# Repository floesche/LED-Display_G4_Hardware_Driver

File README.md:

---
title: Panel PCB 2017
parent: Hardware
grand_parent: Generation 4
---

# G4 Panel

```
├── Design      - OrCAD `.BRD` file
├── Production  - Gerber + BOM
└── Schematic   - pdf with schematic
```

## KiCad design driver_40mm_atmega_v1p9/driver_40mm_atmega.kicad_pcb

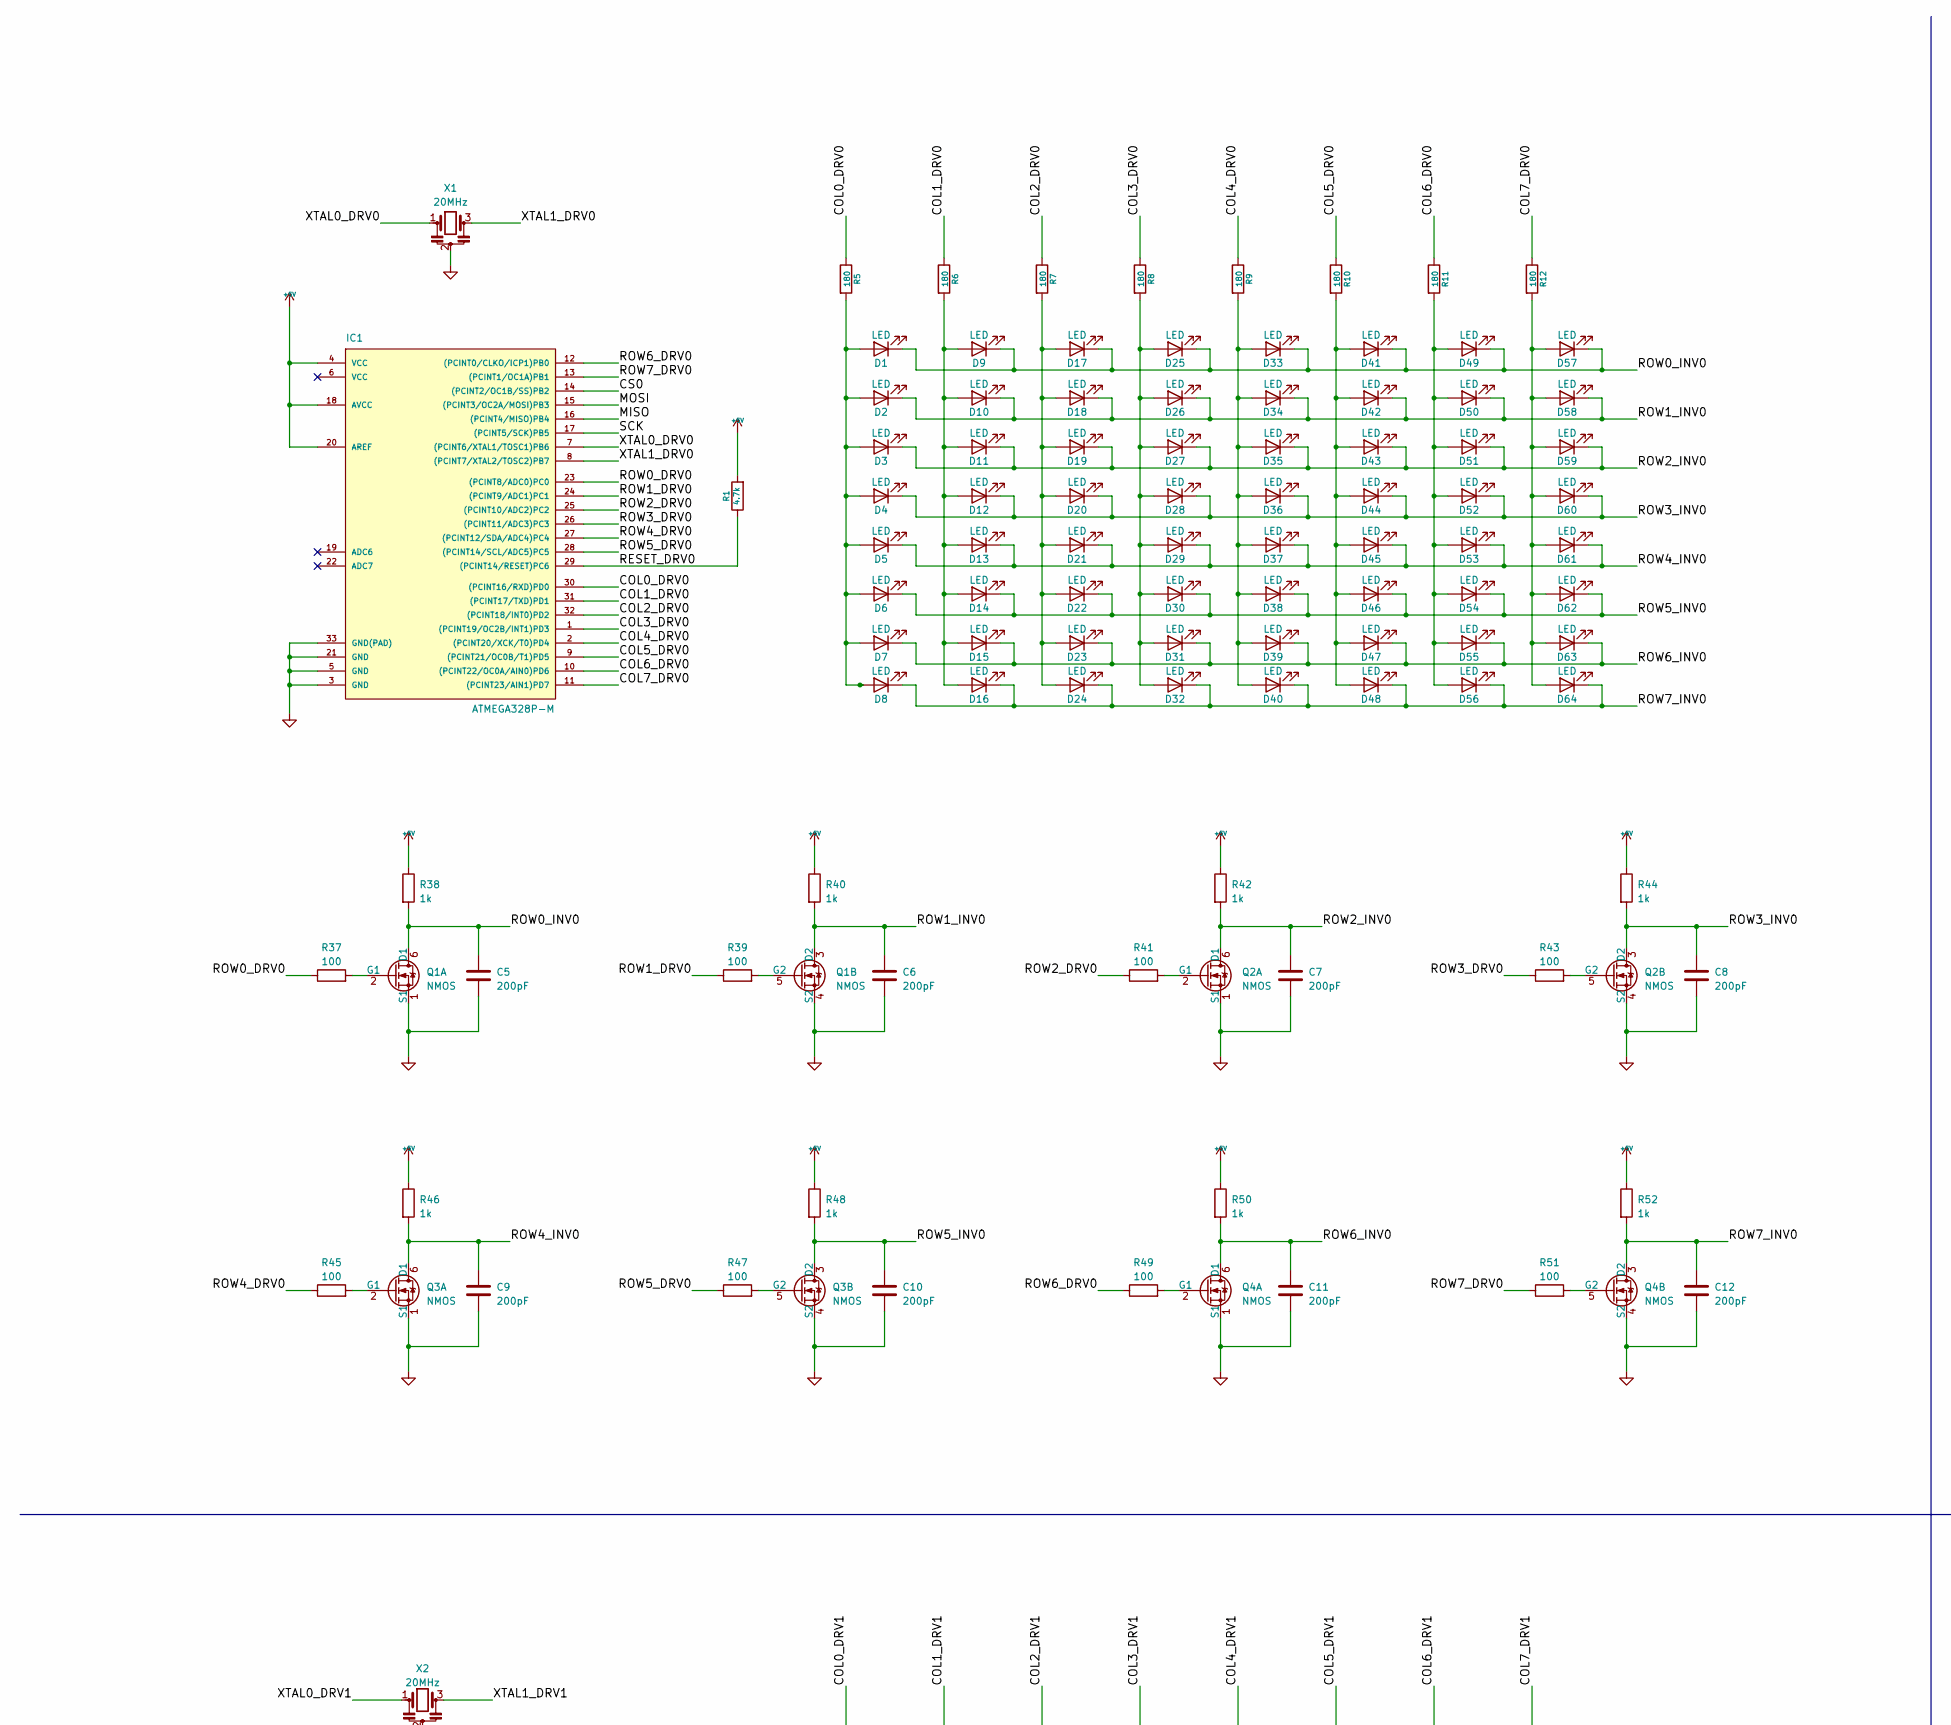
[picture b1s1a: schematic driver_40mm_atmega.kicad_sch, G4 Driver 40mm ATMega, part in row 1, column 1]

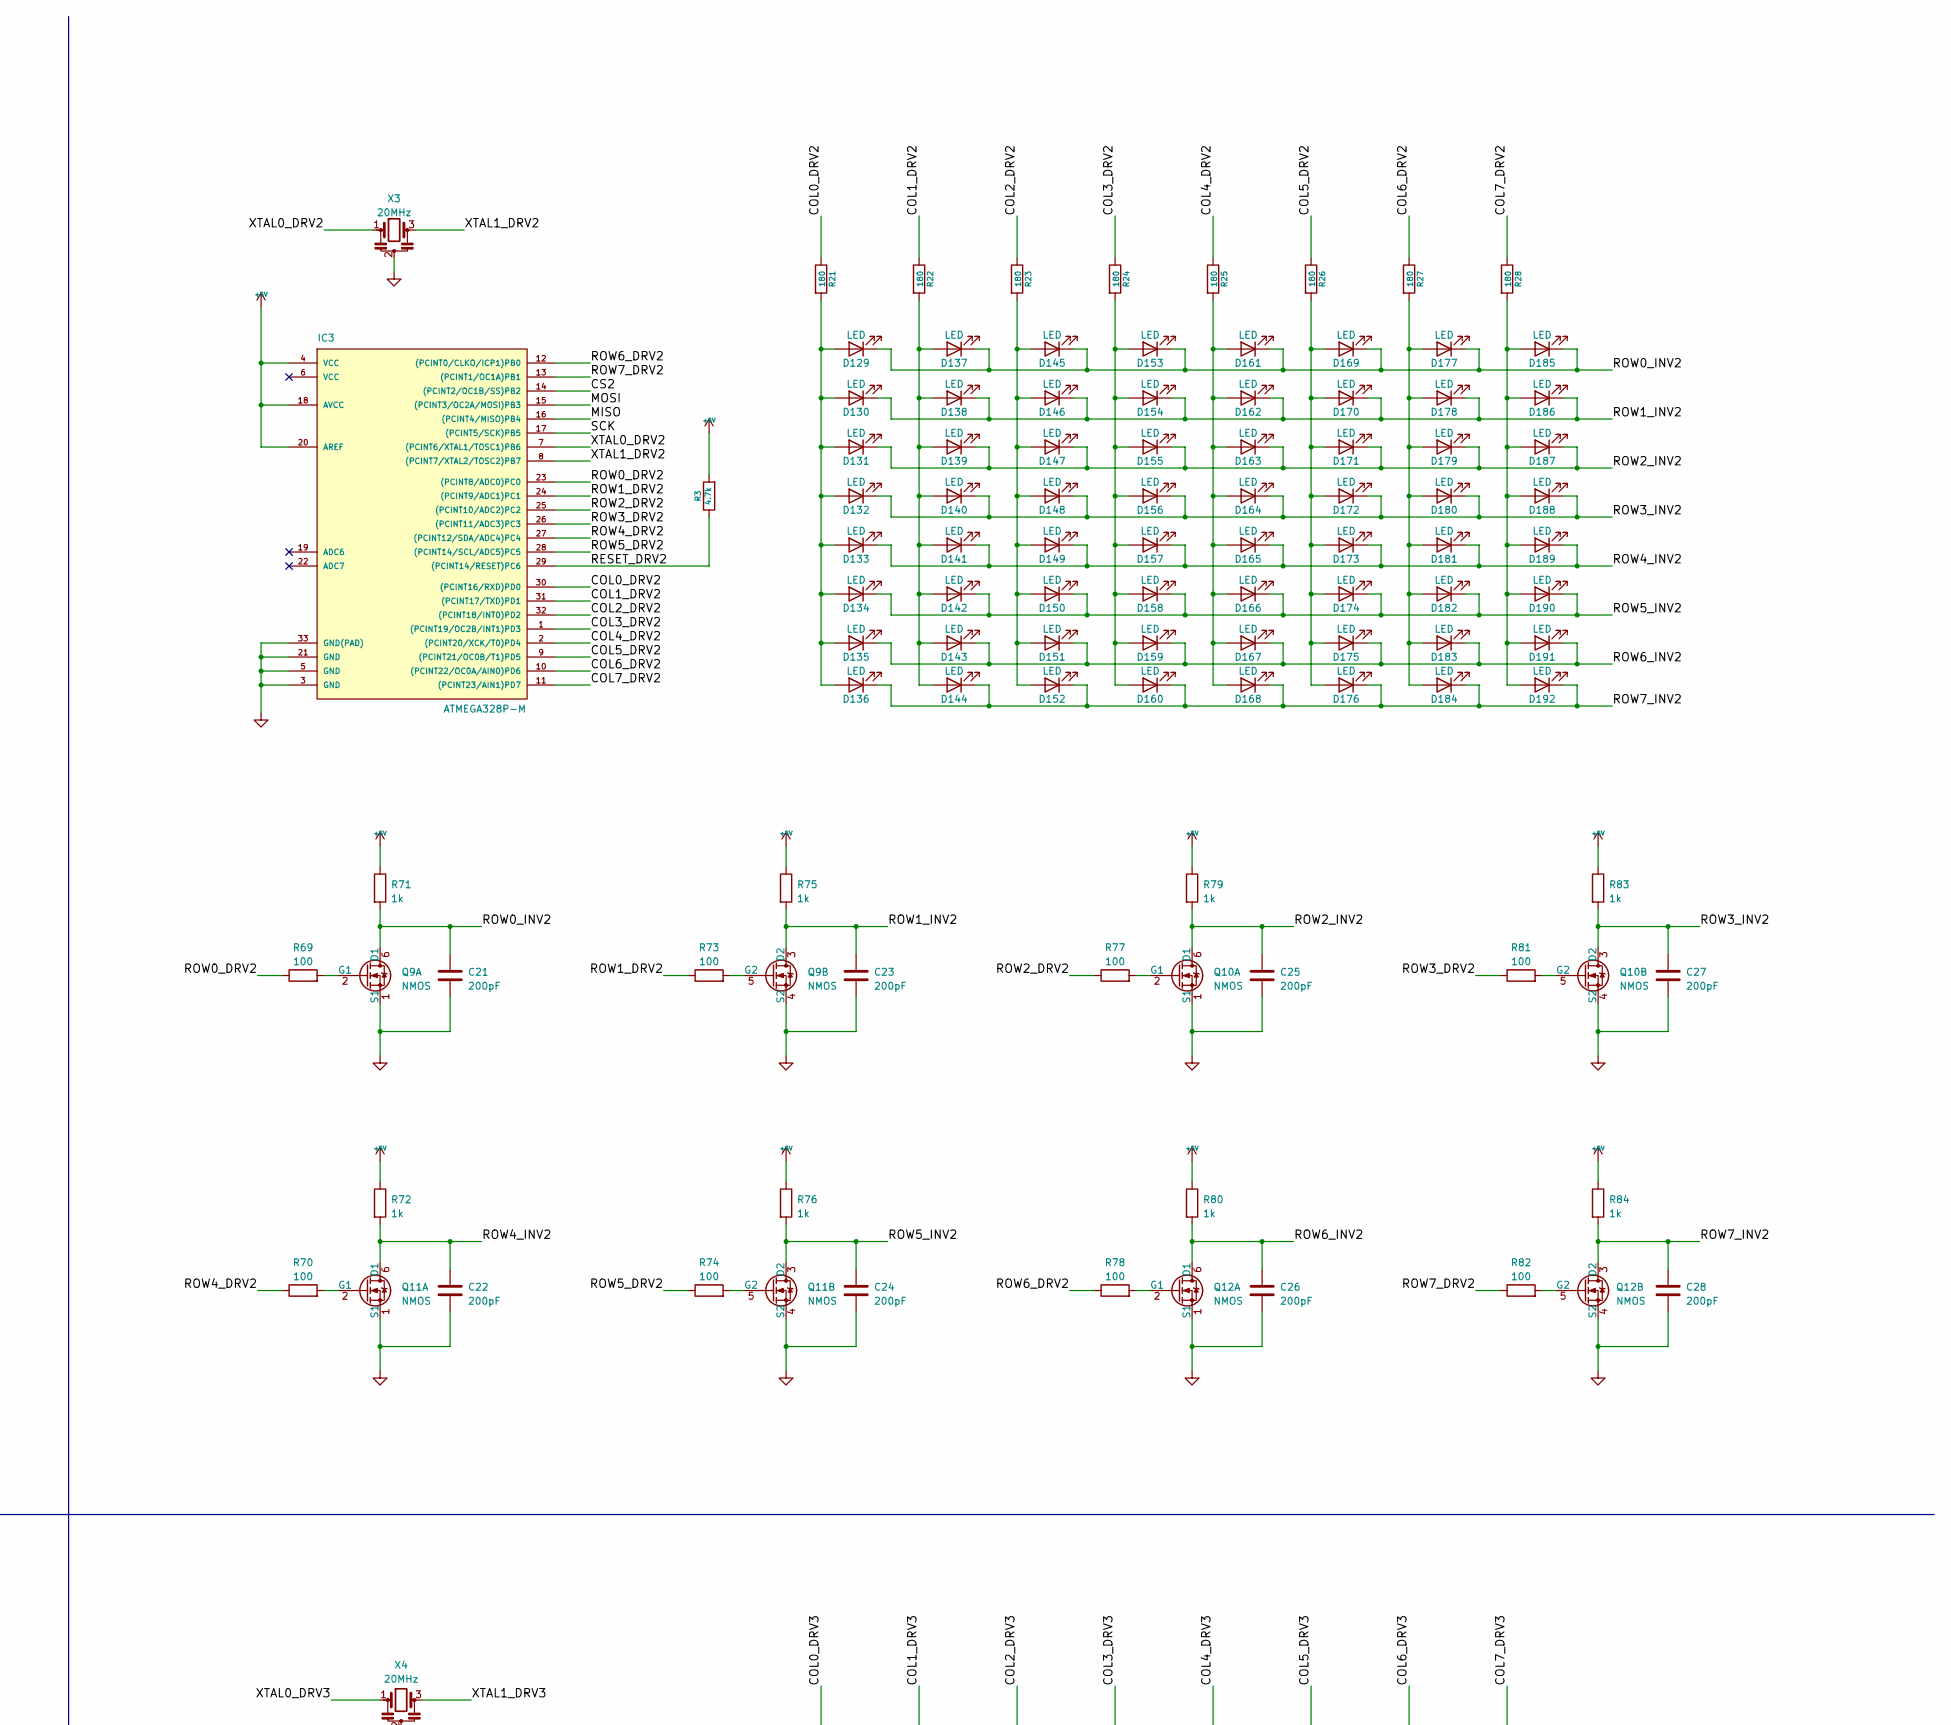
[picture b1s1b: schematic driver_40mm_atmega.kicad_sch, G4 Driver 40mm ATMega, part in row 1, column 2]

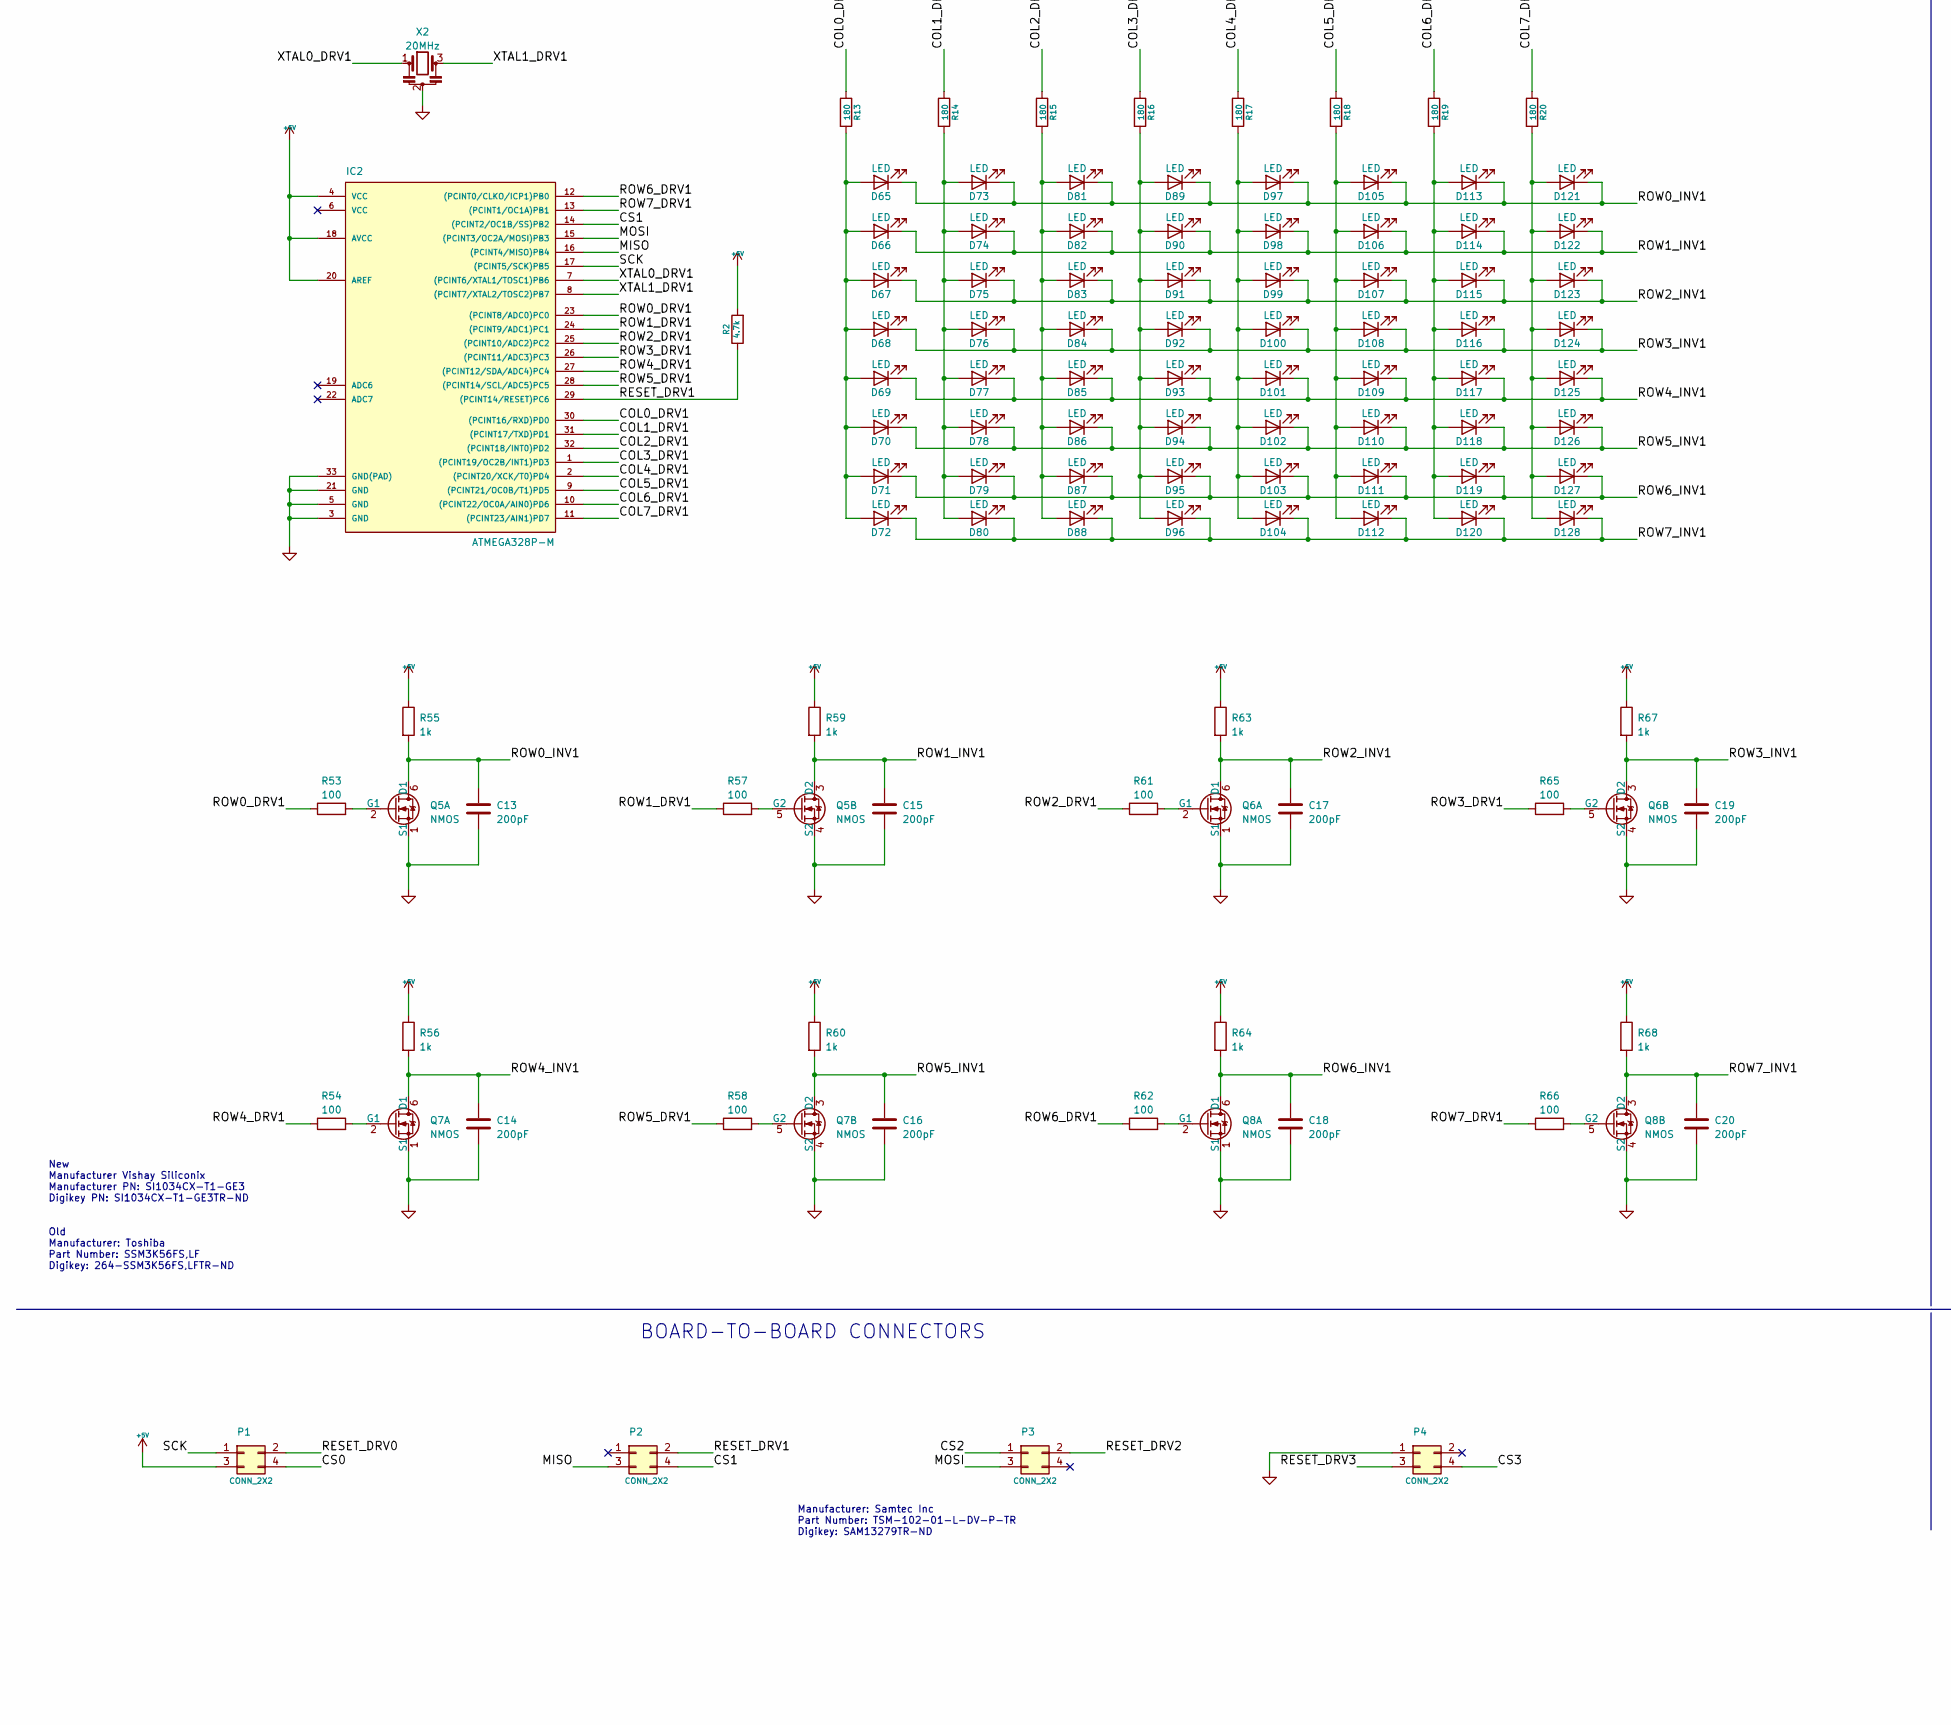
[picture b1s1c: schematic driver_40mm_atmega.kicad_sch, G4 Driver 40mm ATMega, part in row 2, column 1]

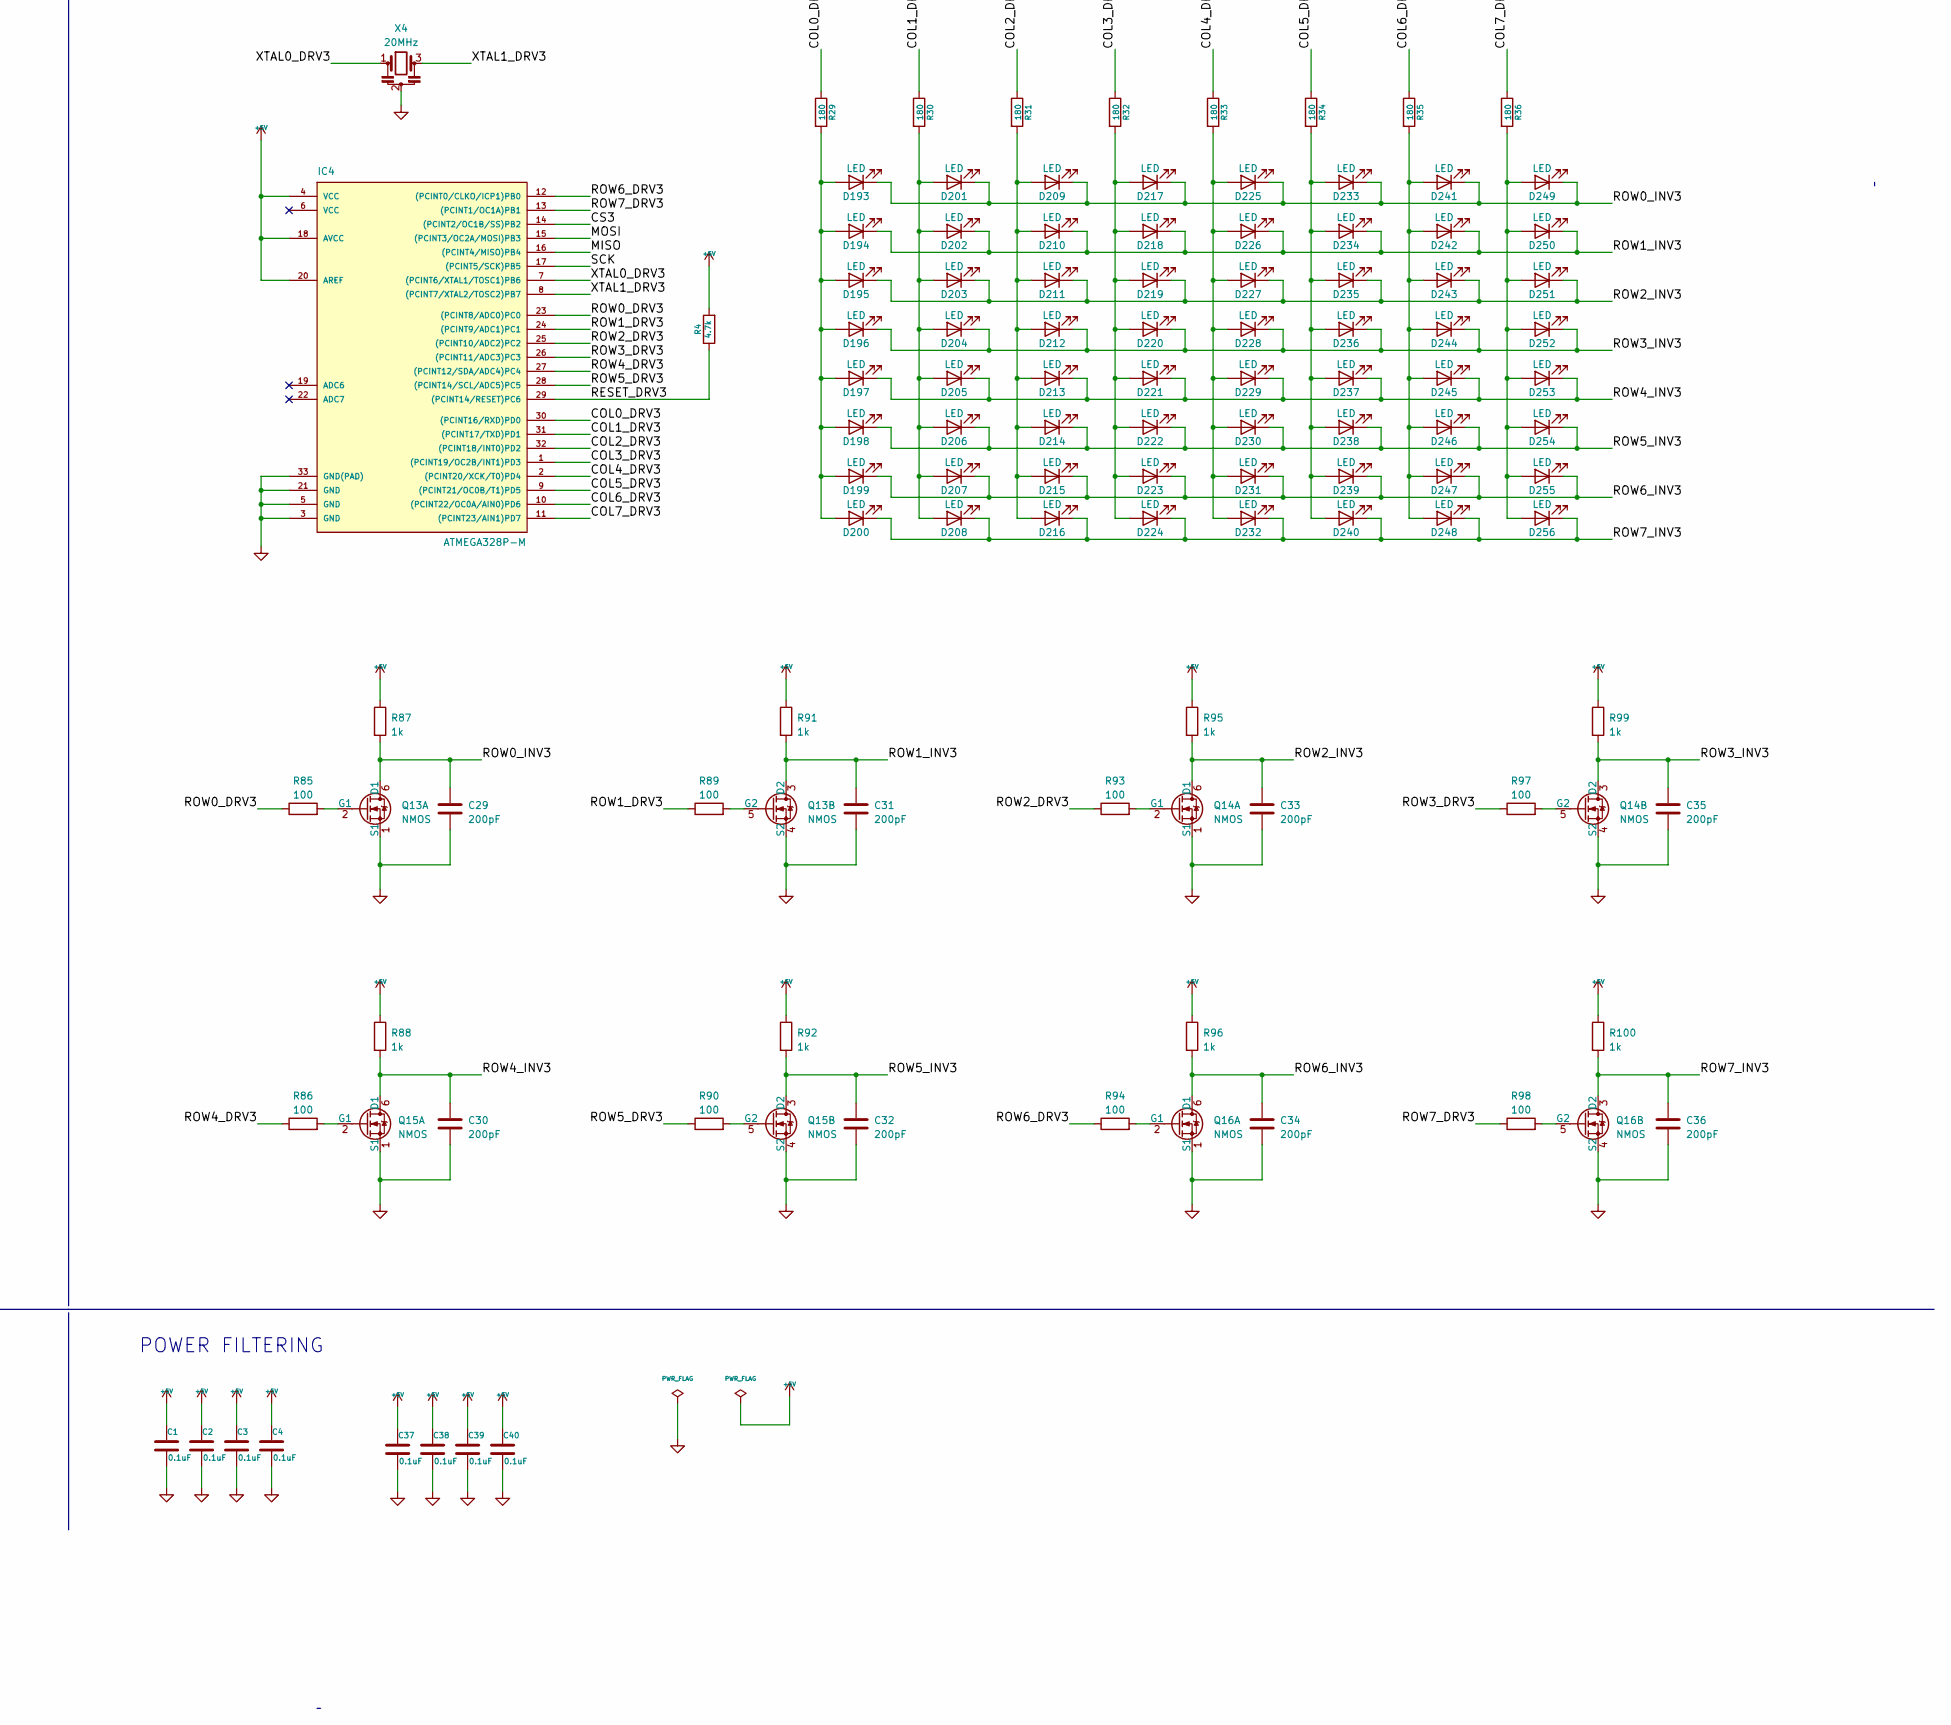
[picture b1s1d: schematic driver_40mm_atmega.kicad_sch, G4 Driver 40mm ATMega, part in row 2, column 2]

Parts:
C1, C2, C3, C4, C37, C38, C39, C40: 0.1uF; C_0201_0603Metric; JLCPCB PN C76937
C5, C6, C7, C8, C9, C10, C11, C12, C13, C14, C15, C16, C17, C18, C19, C20, C21, C22, C23, C24, C25, C26, C27, C28, C29, C30, C31, C32, C33, C34, C35, C36: 200pF; C_0201_0603Metric; JLCPCB PN C565508
D1, D2, D3, D4, D5, D6, D7, D8, D9, D10, D11, D12, D13, D14, D15, D16, D17, D18, D19, D20, D21, D22, D23, D24, D25, D26, D27, D28, D29, D30, D31, D32, D33, D34, D35, D36, D37, D38, D39, D40, D41, D42, D43, D44, D45, D46, D47, D48, D49, D50, D51, D52, D53, D54, D55, D56, D57, D58, D59, D60, D61, D62, D63, D64, D65, D66, D67, D68, D69, D70, D71, D72, D73, D74, D75, D76, D77, D78, D79, D80, D81, D82, D83, D84, D85, D86, D87, D88, D89, D90, D91, D92, D93, D94, D95, D96, D97, D98, D99, D100, D101, D102, D103, D104, D105, D106, D107, D108, D109, D110, D111, D112, D113, D114, D115, D116, D117, D118, D119, D120, D121, D122, D123, D124, D125, D126, D127, D128, D129, D130, D131, D132, D133, D134, D135, D136, D137, D138, D139, D140, D141, D142, D143, D144, D145, D146, D147, D148, D149, D150, D151, D152, D153, D154, D155, D156, D157, D158, D159, D160, D161, D162, D163, D164, D165, D166, D167, D168, D169, D170, D171, D172, D173, D174, D175, D176, D177, D178, D179, D180, D181, D182, D183, D184, D185, D186, D187, D188, D189, D190, D191, D192, D193, D194, D195, D196, D197, D198, D199, D200, D201, D202, D203, D204, D205, D206, D207, D208, D209, D210, D211, D212, D213, D214, D215, D216, D217, D218, D219, D220, D221, D222, D223, D224, D225, D226, D227, D228, D229, D230, D231, D232, D233, D234, D235, D236, D237, D238, D239, D240, D241, D242, D243, D244, D245, D246, D247, D248, D249, D250, D251, D252, D253, D254, D255, D256: LED; LED_0402_1005Metric; JLCPCB PN C5160718
IC1, IC2, IC3, IC4: ATMEGA328P-M; QFN-32-1EP_5x5mm_P0.5mm_EP3.1x3.1mm; JLCPCB PN C2651951
P1, P2, P3, P4: CONN_2X2; PinHeader_2x02_P2.54mm_Vertical_SMD; JLCPCB PN C7499901
Q1, Q2, Q3, Q4, Q5, Q6, Q7, Q8, Q9, Q10, Q11, Q12, Q13, Q14, Q15, Q16: NMOS; SC-89-6; JLCPCB PN C145239
R1, R2, R3, R4: 4.7k; R_0201_0603Metric; JLCPCB PN C226669
R5, R6, R7, R8, R9, R10, R11, R12, R13, R14, R15, R16, R17, R18, R19, R20, R21, R22, R23, R24, R25, R26, R27, R28, R29, R30, R31, R32, R33, R34, R35, R36: 180; R_0201_0603Metric; JLCPCB PN C5141103
R37, R39, R41, R43, R45, R47, R49, R51, R53, R54, R57, R58, R61, R62, R65, R66, R69, R70, R73, R74, R77, R78, R81, R82, R85, R86, R89, R90, R93, R94, R97, R98: 100; R_0201_0603Metric; JLCPCB PN C2991668
R38, R40, R42, R44, R46, R48, R50, R52, R55, R56, R59, R60, R63, R64, R67, R68, R71, R72, R75, R76, R79, R80, R83, R84, R87, R88, R91, R92, R95, R96, R99, R100: 1k; R_0201_0603Metric; JLCPCB PN C102689
X1, X2, X3, X4: 20MHz; Resonator_SMD_Murata_CSTxExxV-3Pin_3.0x1.1mm; JLCPCB PN C882604

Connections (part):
+5V: C1.1, C2.1, C3.1, C4.1, C37.1, C38.1, C39.1, C40.1, IC1.4 (VCC), IC1.18 (AVCC), IC1.20 (AREF), IC2.4 (VCC), IC2.18 (AVCC), IC2.20 (AREF), IC3.4 (VCC), IC3.18 (AVCC), IC3.20 (AREF), IC4.4 (VCC), IC4.18 (AVCC), IC4.20 (AREF), P1.3, R1.2, R2.2, R3.2, R4.2, R38.1, R40.1, R42.1, R44.1, R46.1, R48.1, R50.1, R52.1, R55.1, R56.1, R59.1, R60.1, R63.1, R64.1, R67.1, R68.1, R71.1, R72.1, R75.1, R76.1, R79.1, R80.1, R83.1, R84.1, R87.1, R88.1, R91.1, R92.1, R95.1, R96.1, R99.1, R100.1
/COL0_DRV0: IC1.30 ((PCINT16/RXD)PD0), R5.1
/COL0_DRV1: IC2.30 ((PCINT16/RXD)PD0), R13.1
/COL0_DRV2: IC3.30 ((PCINT16/RXD)PD0), R21.1
/COL0_DRV3: IC4.30 ((PCINT16/RXD)PD0), R29.1
/COL1_DRV0: IC1.31 ((PCINT17/TXD)PD1), R6.1
/COL1_DRV1: IC2.31 ((PCINT17/TXD)PD1), R14.1
/COL1_DRV2: IC3.31 ((PCINT17/TXD)PD1), R22.1
/COL1_DRV3: IC4.31 ((PCINT17/TXD)PD1), R30.1
/COL2_DRV0: IC1.32 ((PCINT18/INT0)PD2), R7.1
/COL2_DRV1: IC2.32 ((PCINT18/INT0)PD2), R15.1
/COL2_DRV2: IC3.32 ((PCINT18/INT0)PD2), R23.1
/COL2_DRV3: IC4.32 ((PCINT18/INT0)PD2), R31.1
/COL3_DRV0: IC1.1 ((PCINT19/OC2B/INT1)PD3), R8.1
/COL3_DRV1: IC2.1 ((PCINT19/OC2B/INT1)PD3), R16.1
/COL3_DRV2: IC3.1 ((PCINT19/OC2B/INT1)PD3), R24.1
/COL3_DRV3: IC4.1 ((PCINT19/OC2B/INT1)PD3), R32.1
/COL4_DRV0: IC1.2 ((PCINT20/XCK/T0)PD4), R9.1
/COL4_DRV1: IC2.2 ((PCINT20/XCK/T0)PD4), R17.1
/COL4_DRV2: IC3.2 ((PCINT20/XCK/T0)PD4), R25.1
/COL4_DRV3: IC4.2 ((PCINT20/XCK/T0)PD4), R33.1
/COL5_DRV0: IC1.9 ((PCINT21/OC0B/T1)PD5), R10.1
/COL5_DRV1: IC2.9 ((PCINT21/OC0B/T1)PD5), R18.1
/COL5_DRV2: IC3.9 ((PCINT21/OC0B/T1)PD5), R26.1
/COL5_DRV3: IC4.9 ((PCINT21/OC0B/T1)PD5), R34.1
/COL6_DRV0: IC1.10 ((PCINT22/OC0A/AIN0)PD6), R11.1
/COL6_DRV1: IC2.10 ((PCINT22/OC0A/AIN0)PD6), R19.1
/COL6_DRV2: IC3.10 ((PCINT22/OC0A/AIN0)PD6), R27.1
/COL6_DRV3: IC4.10 ((PCINT22/OC0A/AIN0)PD6), R35.1
/COL7_DRV0: IC1.11 ((PCINT23/AIN1)PD7), R12.1
/COL7_DRV1: IC2.11 ((PCINT23/AIN1)PD7), R20.1
/COL7_DRV2: IC3.11 ((PCINT23/AIN1)PD7), R28.1
/COL7_DRV3: IC4.11 ((PCINT23/AIN1)PD7), R36.1
/CS0: IC1.14 ((PCINT2/OC1B/SS)PB2), P1.4
/CS1: IC2.14 ((PCINT2/OC1B/SS)PB2), P2.4
/CS2: IC3.14 ((PCINT2/OC1B/SS)PB2), P3.1
/CS3: IC4.14 ((PCINT2/OC1B/SS)PB2), P4.4
/MISO: IC1.16 ((PCINT4/MISO)PB4), IC2.16 ((PCINT4/MISO)PB4), IC3.16 ((PCINT4/MISO)PB4), IC4.16 ((PCINT4/MISO)PB4), P2.3
/MOSI: IC1.15 ((PCINT3/OC2A/MOSI)PB3), IC2.15 ((PCINT3/OC2A/MOSI)PB3), IC3.15 ((PCINT3/OC2A/MOSI)PB3), IC4.15 ((PCINT3/OC2A/MOSI)PB3), P3.3
/RESET_DRV0: IC1.29 ((PCINT14/RESET)PC6), P1.2, R1.1
/RESET_DRV1: IC2.29 ((PCINT14/RESET)PC6), P2.2, R2.1
/RESET_DRV2: IC3.29 ((PCINT14/RESET)PC6), P3.2, R3.1
/RESET_DRV3: IC4.29 ((PCINT14/RESET)PC6), P4.3, R4.1
/ROW0_DRV0: IC1.23 ((PCINT8/ADC0)PC0), R37.1
/ROW0_DRV1: IC2.23 ((PCINT8/ADC0)PC0), R53.1
/ROW0_DRV2: IC3.23 ((PCINT8/ADC0)PC0), R69.1
/ROW0_DRV3: IC4.23 ((PCINT8/ADC0)PC0), R85.1
/ROW0_INV0: C5.1, D1.1 (K), D9.1 (K), D17.1 (K), D25.1 (K), D33.1 (K), D41.1 (K), D49.1 (K), D57.1 (K), Q1.6 (D1), R38.2
/ROW0_INV1: C13.1, D65.1 (K), D73.1 (K), D81.1 (K), D89.1 (K), D97.1 (K), D105.1 (K), D113.1 (K), D121.1 (K), Q5.6 (D1), R55.2
/ROW0_INV2: C21.1, D129.1 (K), D137.1 (K), D145.1 (K), D153.1 (K), D161.1 (K), D169.1 (K), D177.1 (K), D185.1 (K), Q9.6 (D1), R71.2
/ROW0_INV3: C29.1, D193.1 (K), D201.1 (K), D209.1 (K), D217.1 (K), D225.1 (K), D233.1 (K), D241.1 (K), D249.1 (K), Q13.6 (D1), R87.2
/ROW1_DRV0: IC1.24 ((PCINT9/ADC1)PC1), R39.1
/ROW1_DRV1: IC2.24 ((PCINT9/ADC1)PC1), R57.1
/ROW1_DRV2: IC3.24 ((PCINT9/ADC1)PC1), R73.1
/ROW1_DRV3: IC4.24 ((PCINT9/ADC1)PC1), R89.1
/ROW1_INV0: C6.1, D2.1 (K), D10.1 (K), D18.1 (K), D26.1 (K), D34.1 (K), D42.1 (K), D50.1 (K), D58.1 (K), Q1.3 (D2), R40.2
/ROW1_INV1: C15.1, D66.1 (K), D74.1 (K), D82.1 (K), D90.1 (K), D98.1 (K), D106.1 (K), D114.1 (K), D122.1 (K), Q5.3 (D2), R59.2
/ROW1_INV2: C23.1, D130.1 (K), D138.1 (K), D146.1 (K), D154.1 (K), D162.1 (K), D170.1 (K), D178.1 (K), D186.1 (K), Q9.3 (D2), R75.2
/ROW1_INV3: C31.1, D194.1 (K), D202.1 (K), D210.1 (K), D218.1 (K), D226.1 (K), D234.1 (K), D242.1 (K), D250.1 (K), Q13.3 (D2), R91.2
/ROW2_DRV0: IC1.25 ((PCINT10/ADC2)PC2), R41.1
/ROW2_DRV1: IC2.25 ((PCINT10/ADC2)PC2), R61.1
/ROW2_DRV2: IC3.25 ((PCINT10/ADC2)PC2), R77.1
/ROW2_DRV3: IC4.25 ((PCINT10/ADC2)PC2), R93.1
/ROW2_INV0: C7.1, D3.1 (K), D11.1 (K), D19.1 (K), D27.1 (K), D35.1 (K), D43.1 (K), D51.1 (K), D59.1 (K), Q2.6 (D1), R42.2
/ROW2_INV1: C17.1, D67.1 (K), D75.1 (K), D83.1 (K), D91.1 (K), D99.1 (K), D107.1 (K), D115.1 (K), D123.1 (K), Q6.6 (D1), R63.2
/ROW2_INV2: C25.1, D131.1 (K), D139.1 (K), D147.1 (K), D155.1 (K), D163.1 (K), D171.1 (K), D179.1 (K), D187.1 (K), Q10.6 (D1), R79.2
/ROW2_INV3: C33.1, D195.1 (K), D203.1 (K), D211.1 (K), D219.1 (K), D227.1 (K), D235.1 (K), D243.1 (K), D251.1 (K), Q14.6 (D1), R95.2
/ROW3_DRV0: IC1.26 ((PCINT11/ADC3)PC3), R43.1
/ROW3_DRV1: IC2.26 ((PCINT11/ADC3)PC3), R65.1
/ROW3_DRV2: IC3.26 ((PCINT11/ADC3)PC3), R81.1
/ROW3_DRV3: IC4.26 ((PCINT11/ADC3)PC3), R97.1
/ROW3_INV0: C8.1, D4.1 (K), D12.1 (K), D20.1 (K), D28.1 (K), D36.1 (K), D44.1 (K), D52.1 (K), D60.1 (K), Q2.3 (D2), R44.2
/ROW3_INV1: C19.1, D68.1 (K), D76.1 (K), D84.1 (K), D92.1 (K), D100.1 (K), D108.1 (K), D116.1 (K), D124.1 (K), Q6.3 (D2), R67.2
/ROW3_INV2: C27.1, D132.1 (K), D140.1 (K), D148.1 (K), D156.1 (K), D164.1 (K), D172.1 (K), D180.1 (K), D188.1 (K), Q10.3 (D2), R83.2
/ROW3_INV3: C35.1, D196.1 (K), D204.1 (K), D212.1 (K), D220.1 (K), D228.1 (K), D236.1 (K), D244.1 (K), D252.1 (K), Q14.3 (D2), R99.2
/ROW4_DRV0: IC1.27 ((PCINT12/SDA/ADC4)PC4), R45.1
/ROW4_DRV1: IC2.27 ((PCINT12/SDA/ADC4)PC4), R54.1
/ROW4_DRV2: IC3.27 ((PCINT12/SDA/ADC4)PC4), R70.1
/ROW4_DRV3: IC4.27 ((PCINT12/SDA/ADC4)PC4), R86.1
/ROW4_INV0: C9.1, D5.1 (K), D13.1 (K), D21.1 (K), D29.1 (K), D37.1 (K), D45.1 (K), D53.1 (K), D61.1 (K), Q3.6 (D1), R46.2
/ROW4_INV1: C14.1, D69.1 (K), D77.1 (K), D85.1 (K), D93.1 (K), D101.1 (K), D109.1 (K), D117.1 (K), D125.1 (K), Q7.6 (D1), R56.2
/ROW4_INV2: C22.1, D133.1 (K), D141.1 (K), D149.1 (K), D157.1 (K), D165.1 (K), D173.1 (K), D181.1 (K), D189.1 (K), Q11.6 (D1), R72.2
/ROW4_INV3: C30.1, D197.1 (K), D205.1 (K), D213.1 (K), D221.1 (K), D229.1 (K), D237.1 (K), D245.1 (K), D253.1 (K), Q15.6 (D1), R88.2
/ROW5_DRV0: IC1.28 ((PCINT14/SCL/ADC5)PC5), R47.1
/ROW5_DRV1: IC2.28 ((PCINT14/SCL/ADC5)PC5), R58.1
/ROW5_DRV2: IC3.28 ((PCINT14/SCL/ADC5)PC5), R74.1
/ROW5_DRV3: IC4.28 ((PCINT14/SCL/ADC5)PC5), R90.1
/ROW5_INV0: C10.1, D6.1 (K), D14.1 (K), D22.1 (K), D30.1 (K), D38.1 (K), D46.1 (K), D54.1 (K), D62.1 (K), Q3.3 (D2), R48.2
/ROW5_INV1: C16.1, D70.1 (K), D78.1 (K), D86.1 (K), D94.1 (K), D102.1 (K), D110.1 (K), D118.1 (K), D126.1 (K), Q7.3 (D2), R60.2
/ROW5_INV2: C24.1, D134.1 (K), D142.1 (K), D150.1 (K), D158.1 (K), D166.1 (K), D174.1 (K), D182.1 (K), D190.1 (K), Q11.3 (D2), R76.2
/ROW5_INV3: C32.1, D198.1 (K), D206.1 (K), D214.1 (K), D222.1 (K), D230.1 (K), D238.1 (K), D246.1 (K), D254.1 (K), Q15.3 (D2), R92.2
/ROW6_DRV0: IC1.12 ((PCINT0/CLKO/ICP1)PB0), R49.1
/ROW6_DRV1: IC2.12 ((PCINT0/CLKO/ICP1)PB0), R62.1
/ROW6_DRV2: IC3.12 ((PCINT0/CLKO/ICP1)PB0), R78.1
/ROW6_DRV3: IC4.12 ((PCINT0/CLKO/ICP1)PB0), R94.1
/ROW6_INV0: C11.1, D7.1 (K), D15.1 (K), D23.1 (K), D31.1 (K), D39.1 (K), D47.1 (K), D55.1 (K), D63.1 (K), Q4.6 (D1), R50.2
/ROW6_INV1: C18.1, D71.1 (K), D79.1 (K), D87.1 (K), D95.1 (K), D103.1 (K), D111.1 (K), D119.1 (K), D127.1 (K), Q8.6 (D1), R64.2
/ROW6_INV2: C26.1, D135.1 (K), D143.1 (K), D151.1 (K), D159.1 (K), D167.1 (K), D175.1 (K), D183.1 (K), D191.1 (K), Q12.6 (D1), R80.2
/ROW6_INV3: C34.1, D199.1 (K), D207.1 (K), D215.1 (K), D223.1 (K), D231.1 (K), D239.1 (K), D247.1 (K), D255.1 (K), Q16.6 (D1), R96.2
/ROW7_DRV0: IC1.13 ((PCINT1/OC1A)PB1), R51.1
/ROW7_DRV1: IC2.13 ((PCINT1/OC1A)PB1), R66.1
/ROW7_DRV2: IC3.13 ((PCINT1/OC1A)PB1), R82.1
/ROW7_DRV3: IC4.13 ((PCINT1/OC1A)PB1), R98.1
/ROW7_INV0: C12.1, D8.1 (K), D16.1 (K), D24.1 (K), D32.1 (K), D40.1 (K), D48.1 (K), D56.1 (K), D64.1 (K), Q4.3 (D2), R52.2
/ROW7_INV1: C20.1, D72.1 (K), D80.1 (K), D88.1 (K), D96.1 (K), D104.1 (K), D112.1 (K), D120.1 (K), D128.1 (K), Q8.3 (D2), R68.2
/ROW7_INV2: C28.1, D136.1 (K), D144.1 (K), D152.1 (K), D160.1 (K), D168.1 (K), D176.1 (K), D184.1 (K), D192.1 (K), Q12.3 (D2), R84.2
/ROW7_INV3: C36.1, D200.1 (K), D208.1 (K), D216.1 (K), D224.1 (K), D232.1 (K), D240.1 (K), D248.1 (K), D256.1 (K), Q16.3 (D2), R100.2
/SCK: IC1.17 ((PCINT5/SCK)PB5), IC2.17 ((PCINT5/SCK)PB5), IC3.17 ((PCINT5/SCK)PB5), IC4.17 ((PCINT5/SCK)PB5), P1.1
/XTAL0_DRV0: IC1.7 ((PCINT6/XTAL1/TOSC1)PB6), X1.1
/XTAL0_DRV1: IC2.7 ((PCINT6/XTAL1/TOSC1)PB6), X2.1
/XTAL0_DRV2: IC3.7 ((PCINT6/XTAL1/TOSC1)PB6), X3.1
/XTAL0_DRV3: IC4.7 ((PCINT6/XTAL1/TOSC1)PB6), X4.1
/XTAL1_DRV0: IC1.8 ((PCINT7/XTAL2/TOSC2)PB7), X1.3
/XTAL1_DRV1: IC2.8 ((PCINT7/XTAL2/TOSC2)PB7), X2.3
/XTAL1_DRV2: IC3.8 ((PCINT7/XTAL2/TOSC2)PB7), X3.3
/XTAL1_DRV3: IC4.8 ((PCINT7/XTAL2/TOSC2)PB7), X4.3
GND: C1.2, C2.2, C3.2, C4.2, C5.2, C6.2, C7.2, C8.2, C9.2, C10.2, C11.2, C12.2, C13.2, C14.2, C15.2, C16.2, C17.2, C18.2, C19.2, C20.2, C21.2, C22.2, C23.2, C24.2, C25.2, C26.2, C27.2, C28.2, C29.2, C30.2, C31.2, C32.2, C33.2, C34.2, C35.2, C36.2, C37.2, C38.2, C39.2, C40.2, IC1.3 (GND), IC1.5 (GND), IC1.21 (GND), IC1.33 (GND(PAD)), IC2.3 (GND), IC2.5 (GND), IC2.21 (GND), IC2.33 (GND(PAD)), IC3.3 (GND), IC3.5 (GND), IC3.21 (GND), IC3.33 (GND(PAD)), IC4.3 (GND), IC4.5 (GND), IC4.21 (GND), IC4.33 (GND(PAD)), P4.1, Q1.1 (S1), Q1.4 (S2), Q2.1 (S1), Q2.4 (S2), Q3.1 (S1), Q3.4 (S2), Q4.1 (S1), Q4.4 (S2), Q5.1 (S1), Q5.4 (S2), Q6.1 (S1), Q6.4 (S2), Q7.1 (S1), Q7.4 (S2), Q8.1 (S1), Q8.4 (S2), Q9.1 (S1), Q9.4 (S2), Q10.1 (S1), Q10.4 (S2), Q11.1 (S1), Q11.4 (S2), Q12.1 (S1), Q12.4 (S2), Q13.1 (S1), Q13.4 (S2), Q14.1 (S1), Q14.4 (S2), Q15.1 (S1)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
unnamed: D1.2 (A), D2.2 (A), D3.2 (A), D4.2 (A), D5.2 (A), D6.2 (A), D7.2 (A), D8.2 (A), R5.2
unnamed: D9.2 (A), D10.2 (A), D11.2 (A), D12.2 (A), D13.2 (A), D14.2 (A), D15.2 (A), D16.2 (A), R6.2
unnamed: D17.2 (A), D18.2 (A), D19.2 (A), D20.2 (A), D21.2 (A), D22.2 (A), D23.2 (A), D24.2 (A), R7.2
unnamed: D25.2 (A), D26.2 (A), D27.2 (A), D28.2 (A), D29.2 (A), D30.2 (A), D31.2 (A), D32.2 (A), R8.2
unnamed: D33.2 (A), D34.2 (A), D35.2 (A), D36.2 (A), D37.2 (A), D38.2 (A), D39.2 (A), D40.2 (A), R9.2
unnamed: D41.2 (A), D42.2 (A), D43.2 (A), D44.2 (A), D45.2 (A), D46.2 (A), D47.2 (A), D48.2 (A), R10.2
unnamed: D49.2 (A), D50.2 (A), D51.2 (A), D52.2 (A), D53.2 (A), D54.2 (A), D55.2 (A), D56.2 (A), R11.2
unnamed: D57.2 (A), D58.2 (A), D59.2 (A), D60.2 (A), D61.2 (A), D62.2 (A), D63.2 (A), D64.2 (A), R12.2
unnamed: D65.2 (A), D66.2 (A), D67.2 (A), D68.2 (A), D69.2 (A), D70.2 (A), D71.2 (A), D72.2 (A), R13.2
unnamed: D73.2 (A), D74.2 (A), D75.2 (A), D76.2 (A), D77.2 (A), D78.2 (A), D79.2 (A), D80.2 (A), R14.2
unnamed: D81.2 (A), D82.2 (A), D83.2 (A), D84.2 (A), D85.2 (A), D86.2 (A), D87.2 (A), D88.2 (A), R15.2
unnamed: D89.2 (A), D90.2 (A), D91.2 (A), D92.2 (A), D93.2 (A), D94.2 (A), D95.2 (A), D96.2 (A), R16.2
unnamed: D97.2 (A), D98.2 (A), D99.2 (A), D100.2 (A), D101.2 (A), D102.2 (A), D103.2 (A), D104.2 (A), R17.2
unnamed: D105.2 (A), D106.2 (A), D107.2 (A), D108.2 (A), D109.2 (A), D110.2 (A), D111.2 (A), D112.2 (A), R18.2
unnamed: D113.2 (A), D114.2 (A), D115.2 (A), D116.2 (A), D117.2 (A), D118.2 (A), D119.2 (A), D120.2 (A), R19.2
unnamed: D121.2 (A), D122.2 (A), D123.2 (A), D124.2 (A), D125.2 (A), D126.2 (A), D127.2 (A), D128.2 (A), R20.2
unnamed: D129.2 (A), D130.2 (A), D131.2 (A), D132.2 (A), D133.2 (A), D134.2 (A), D135.2 (A), D136.2 (A), R21.2
unnamed: D137.2 (A), D138.2 (A), D139.2 (A), D140.2 (A), D141.2 (A), D142.2 (A), D143.2 (A), D144.2 (A), R22.2
unnamed: D145.2 (A), D146.2 (A), D147.2 (A), D148.2 (A), D149.2 (A), D150.2 (A), D151.2 (A), D152.2 (A), R23.2
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
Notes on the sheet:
Manufacturer: Samtec Inc Part Number: TSM-102-01-L-DV-P-TR Digikey: SAM13279TR-ND
POWER FILTERING
New Manufacturer Vishay Siliconix Manufacturer PN: SI1034CX-T1-GE3 Digikey PN: SI1034CX-T1-GE3TR-ND Old Manufacturer: Toshiba Part Number: SSM3K56FS,LF Digikey: 264-SSM3K56FS,LFTR-ND
BOARD-TO-BOARD CONNECTORS

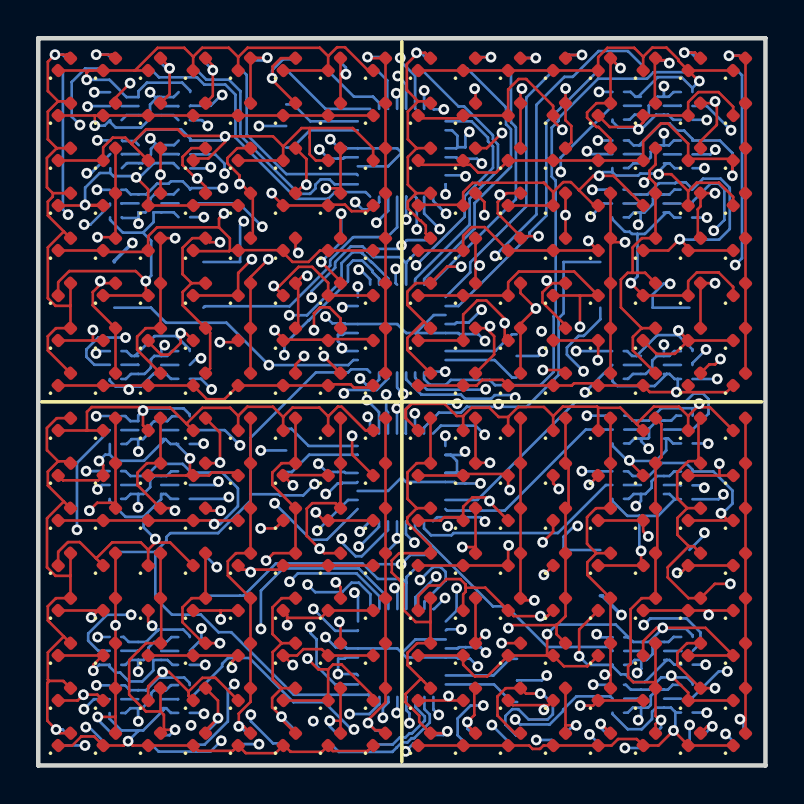
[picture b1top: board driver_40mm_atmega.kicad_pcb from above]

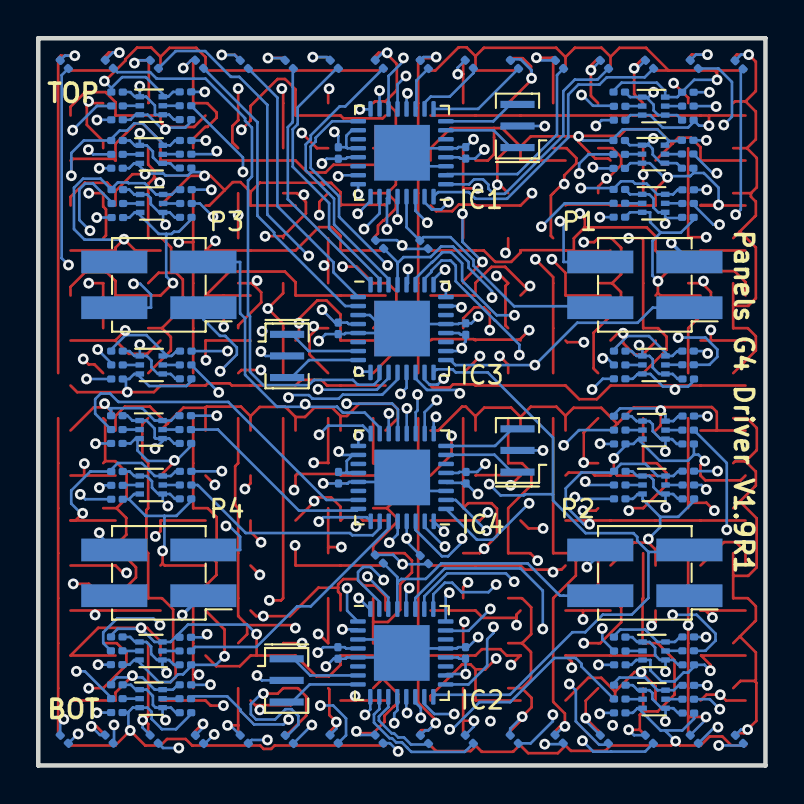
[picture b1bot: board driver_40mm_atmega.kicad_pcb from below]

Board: 6 copper layers, 40.4 x 40.4 mm, 424 parts (168 on the bottom side), 181 nets.
